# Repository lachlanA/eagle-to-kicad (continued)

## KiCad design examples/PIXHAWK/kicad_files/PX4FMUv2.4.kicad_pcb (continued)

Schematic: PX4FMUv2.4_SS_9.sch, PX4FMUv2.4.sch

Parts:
C901, C902, C903: 0u1; PIXHAWK2_0402-CAP
D1: MSS1P4-M3; PIXHAWK2_MICROSMP
D901, D902, D903: PESD0402-140; PIXHAWK2_0402-TVS
J901: PIXHAWK2_3X16RA
L901: KNH16C104DA5TS; PIXHAWK2_KYOCERA-KNH16-DA
R901: 10K; PIXHAWK2_0402-RES
R902, R903, R904, R905, R906, R907, R908, R909, R910, R911, R912, R913, R914, R915, R916, R917: 220R; PIXHAWK2_0402-RES
R918, R919, R922: 10K/0.1%; PIXHAWK2_0402-RES
U901, U902: TXS0108QFN20; PIXHAWK2_QFN20-RGY
U903: 74LVC2G240; PIXHAWK2_TSSOP8_SOT505-2

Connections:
!SBUS_OUTPUT_EN: U903.7 (!2OE); also elsewhere on the board
FMU-CH1: U901.7 (A6); also elsewhere on the board
FMU-CH1-PROT: J901.46, R913.P$2 (2)
FMU-CH2: U901.6 (A5); also elsewhere on the board
FMU-CH3: U901.5 (A4); also elsewhere on the board
FMU-CH4: U901.4 (A3); also elsewhere on the board
FMU-CH5: U901.3 (A2); also elsewhere on the board
FMU-CH6: U901.1 (A1); also elsewhere on the board
FMU-CH6-PROT: J901.31, R902.P$2 (2)
FMU-VDD_3V3: C902.P$1 (1), U901.2 (VCCA), U901.10 (OE), U901.19 (VCCB); also elsewhere on the board
GND: C901.P$2 (2), C902.P$2 (2), C903.P$2 (2), D901.A, D902.A, D903.A, J901.3, J901.6, J901.9, J901.12, J901.15, J901.18, J901.21, J901.24, J901.27, J901.30, J901.33, J901.36, J901.39, J901.42, J901.45, J901.48, L901.P$3, L901.P$4, L901.P$5, R919.P$1 (1), U901.11 (GND), U902.11 (GND), U903.1 (!1OE), U903.4 (GND); also elsewhere on the board
IO-CH1: U902.9 (A8); also elsewhere on the board
IO-CH1-PROT: J901.28, R917.P$2 (2)
IO-CH2: U902.8 (A7); also elsewhere on the board
IO-CH3: U902.7 (A6); also elsewhere on the board
IO-CH4: U902.6 (A5); also elsewhere on the board
IO-CH5: U902.5 (A4); also elsewhere on the board
IO-CH6: U902.4 (A3); also elsewhere on the board
IO-CH7: U902.3 (A2); also elsewhere on the board
IO-CH8: U902.1 (A1); also elsewhere on the board
IO-CH8-PROT: J901.7, R905.P$2 (2)
IO-VDD_3V3: C901.P$1 (1), C903.P$1 (1), U902.2 (VCCA), U902.10 (OE), U902.19 (VCCB), U903.8 (VCC); also elsewhere on the board
IO-VDD_5V5: J901.2; also elsewhere on the board
unnamed: R918.P$2 (2), R922.P$1 (1)
unnamed: J901.10, R914.P$2 (2)
unnamed: D902.C, R901.P$2 (2), R910.P$1 (1), U903.3 (2Y)
unnamed: R905.P$1 (1), U902.20 (B1)
unnamed: R914.P$1 (1), U902.18 (B2)
unnamed: R906.P$1 (1), U902.17 (B3)
unnamed: R915.P$1 (1), U902.16 (B4)
unnamed: R907.P$1 (1), U902.15 (B5)
unnamed: R916.P$1 (1), U902.14 (B6)
unnamed: R908.P$1 (1), U902.13 (B7)
unnamed: R917.P$1 (1), U902.12 (B8)
unnamed: R902.P$1 (1), U901.20 (B1)
unnamed: R911.P$1 (1), U901.18 (B2)
unnamed: R903.P$1 (1), U901.17 (B3)
unnamed: R912.P$1 (1), U901.16 (B4)
unnamed: R904.P$1 (1), U901.15 (B5)
unnamed: R913.P$1 (1), U901.14 (B6)
unnamed: J901.34, R911.P$2 (2)
unnamed: J901.13, R906.P$2 (2)
unnamed: J901.16, R915.P$2 (2)
unnamed: J901.19, R907.P$2 (2)
unnamed: J901.22, R916.P$2 (2)
unnamed: J901.25, R908.P$2 (2)
unnamed: J901.37, R903.P$2 (2)
unnamed: J901.40, R912.P$2 (2)
unnamed: J901.43, R904.P$2 (2)
unnamed: J901.4, R910.P$2 (2)
unnamed: D1.CATH (C), D903.C, L901.P$1
PPM-SBUS-PROT: J901.1, R909.P$2 (2)
PPM_INPUT: D901.C, R909.P$1 (1), U903.2 (1A); also elsewhere on the board
RSSI_IN: R901.P$1 (1); also elsewhere on the board
SBUS_INPUT: U903.6 (1Y); also elsewhere on the board
SBUS_OUTPUT: U903.5 (2A); also elsewhere on the board
VDD_SERVO: D1.ANOD (A), J901.5, J901.8, J901.11, J901.14, J901.17, J901.20, J901.23, J901.26, J901.29, J901.32, J901.35, J901.38, J901.41, J901.44, J901.47, R922.P$2 (2); also elsewhere on the board
VDD_SERVO_IN: L901.P$2; also elsewhere on the board
VDD_SERVO_SENS: R918.P$1 (1), R919.P$2 (2); also elsewhere on the board

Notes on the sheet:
Servo Header S.Bus interface
S.Bus in/out
Servo outputs

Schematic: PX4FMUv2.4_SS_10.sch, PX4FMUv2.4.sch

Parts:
C1001: 10u/25V; PIXHAWK2_0805-CAP
C1002: 10n; PIXHAWK2_0402-CAP
C1003: 1u0; PIXHAWK2_0603-CAP
C1004: 10u; PIXHAWK2_0603-CAP
C1005: 0u1F; PIXHAWK2_0402-CAP
C1008: 2u2; PIXHAWK2_0402-CAP
D1001: PMEG2005CT; PIXHAWK2_SOT23-3
F1001: 0ZCA0035FF2G; PIXHAWK2_PTC-1206
R1001: 100K; PIXHAWK2_0402-RES
R1002: 10K; PIXHAWK2_0402-RES
U1001: BQ24313; PIXHAWK2_QFN8-DSG
U1002: MIC5332; PIXHAWK2_MLF-8-EPAD

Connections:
GND: C1001.P$2 (2), C1002.P$2 (2), C1003.P$2 (2), C1004.P$2 (2), C1005.P$2 (2), C1008.P$2 (2), R1001.P$1 (1), R1002.P$1 (1), U1001.2 (VSS), U1001.5 (!CE), U1001.6 (VBAT), U1001.GND (VSS), U1001.P$2 (VSS), U1001.P$3 (VSS), U1002.2 (GND), U1002.GND; also elsewhere on the board
IO-!RESET: U1002.3 (POR2); also elsewhere on the board
IO-!VDD_SERVO_IN_FAULT: U1001.4 (!FAULT); also elsewhere on the board
IO-VDD_3V3: C1003.P$1 (1), C1004.P$1 (1), U1002.7 (VOUT2); also elsewhere on the board
IO-VDD_5V5: C1001.P$1 (1), C1005.P$1 (1), D1001.3 (CC), U1002.1 (VIN), U1002.4 (EN2); also elsewhere on the board
unnamed: D1001.2 (A2), U1001.8 (OUT)
unnamed: R1001.P$2 (2), U1001.7 (ILIM)
unnamed: D1001.1 (A1), F1001.2
unnamed: C1002.P$1 (1), U1002.6 (CSET)
VDD_3V3_SPEKTRUM: C1008.P$1 (1), U1002.8 (VOUT1); also elsewhere on the board
VDD_3V3_SPEKTRUM_EN: R1002.P$2 (2), U1002.5 (EN1); also elsewhere on the board
VDD_5V_IN: F1001.1; also elsewhere on the board
VDD_SERVO_IN: U1001.1 (IN); also elsewhere on the board

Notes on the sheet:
Dual supply from servo rail and FMU 5V rail
Current limit = 25 / Rilim (current in A, R in kOhms) 100K = 250mA
IO Power Supply
Reset output 1s / uF 10n = 10ms delay from power good to reset de-asserted.
Output voltage limited to 5.5V for input voltages up to 10.5V; output switches off at higher input voltages.

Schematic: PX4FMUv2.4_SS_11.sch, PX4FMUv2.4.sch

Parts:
C1101, C1102, C1103: 22u/25V; PIXHAWK2_0805-CAP
C1104: 100u; PIXHAWK2_1206-CAP
C1105, C1106, C1107: 0u1; PIXHAWK2_0402-CAP
C1108, C1109, C1110: 1000p/25V; PIXHAWK2_0402-CAP
J601: DF13C-6P-1.25V; CON-HIROSE-DF13_DF13C-6P-1.25V
L1101, L1102: KNH16C104DA5TS; PIXHAWK2_KYOCERA-KNH16-DA
R1101, R1102: 10K/0.1%; PIXHAWK2_0402-RES
R1103, R1104: 1M; PIXHAWK2_0402-RES
R1105, R1109, R1112: 453K; PIXHAWK2_0402-RES
R1106, R1110, R1113: 56K; PIXHAWK2_0402-RES
R1107, R1111, R1114: 105K; PIXHAWK2_0402-RES
R1115: 0R; PIXHAWK2_0402-RES
RN1101: 1M; RESISTOR-DIL_EXB28V
U1101: LTC4417; PIXHAWK2_MO-220
U1102, U1103, U1104: NTHD4102PT1G; PIXHAWK2_1206-8

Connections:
!VBUS_VALID: RN1101.2 (1), U1101.P$9 (!VALID3); also elsewhere on the board
!VDD_BRICK_VALID: RN1101.4 (1), U1101.P$7 (!VALID1); also elsewhere on the board
!VDD_SERVO_VALID: RN1101.3 (1), U1101.P$8 (!VALID2); also elsewhere on the board
BATT_CURRENT_SENS: R1101.P$1 (1); also elsewhere on the board
BATT_CURRENT_SENS_PROT: J601.3, L1101.P$1, R1104.P$1 (1)
BATT_VOLTAGE_SENS: R1102.P$1 (1); also elsewhere on the board
BATT_VOLTAGE_SENS_PROT: J601.4, L1102.P$1, R1103.P$1 (1)
GND: C1101.P$2 (2), C1102.P$2 (2), C1103.P$2 (2), C1104.P$2 (2), C1105.P$2 (2), C1106.P$2 (2), C1107.P$2 (2), C1108.P$2 (2), C1109.P$2 (2), C1110.P$2 (2), J601.5, J601.6, L1101.P$3, L1101.P$4, L1101.P$5, L1102.P$3, L1102.P$4, L1102.P$5, R1103.P$2 (2), R1104.P$2 (2), R1107.P$2 (2), R1111.P$2 (2), R1114.P$2 (2), R1115.P$1 (1), U1101.P$10 (GND), U1101.P$25 (GND); also elsewhere on the board
unnamed: C1108.P$1 (1), R1105.P$2 (2), R1106.P$1 (1), U1101.P$1 (UV1)
unnamed: R1106.P$2 (2), R1107.P$1 (1), U1101.P$2 (OV1)
unnamed: C1109.P$1 (1), R1109.P$2 (2), R1110.P$1 (1), U1101.P$3 (UV2)
unnamed: R1110.P$2 (2), R1111.P$1 (1), U1101.P$4 (OV2)
unnamed: R1113.P$2 (2), R1114.P$1 (1), U1101.P$6 (OV3)
unnamed: C1110.P$1 (1), R1112.P$2 (2), R1113.P$1 (1), U1101.P$5 (UV3)
unnamed: C1105.P$1 (1), U1101.P$18 (VS1), U1102.P$1 (S), U1102.P$3 (S)
unnamed: L1102.P$2, R1102.P$2 (2)
unnamed: L1101.P$2, R1101.P$2 (2)
unnamed: R1115.P$2 (2), U1101.P$24 (HYS)
unnamed: C1106.P$1 (1), U1101.P$16 (VS2), U1103.P$1 (S), U1103.P$3 (S)
unnamed: C1107.P$1 (1), U1101.P$14 (VS3), U1104.P$1 (S), U1104.P$3 (S)
unnamed: U1101.P$13 (G3), U1104.P$2 (G), U1104.P$4 (G)
unnamed: U1101.P$15 (G2), U1103.P$2 (G), U1103.P$4 (G)
unnamed: U1101.P$17 (G1), U1102.P$2 (G), U1102.P$4 (G)
VBUS: C1103.P$1 (1), R1112.P$1 (1), U1101.P$19 (V3), U1104.P$7 (D), U1104.P$8 (D); also elsewhere on the board
VDD_5V_BRICK: C1101.P$1 (1), J601.1, J601.2, R1105.P$1 (1), U1101.P$21 (V1), U1102.P$7 (D), U1102.P$8 (D); also elsewhere on the board
VDD_5V_IN: C1104.P$1 (1), RN1101.5 (2), RN1101.6 (2), RN1101.7 (2), U1101.P$12 (VOUT), U1102.P$5 (D), U1102.P$6 (D), U1103.P$5 (D), U1103.P$6 (D), U1104.P$5 (D), U1104.P$6 (D); also elsewhere on the board
VDD_SERVO: C1102.P$1 (1), R1109.P$1 (1), U1101.P$20 (V2), U1103.P$7 (D), U1103.P$8 (D); also elsewhere on the board

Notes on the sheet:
Power source selector
Resistors picked so that undervoltage lockout starts at 4.0V and overvoltage lockout at 5.75V. Use 1% or better accuracy!
POWER PATH CONTROLLER: Does enable output if valid for continous 256 ms

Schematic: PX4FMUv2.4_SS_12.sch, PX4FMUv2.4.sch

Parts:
!VBUS_VALID1116: PAD.04; PIXHAWK2_PAD.04X.04
!VDD_BRICK_VALID1116: PAD.04; PIXHAWK2_PAD.04X.04
!VDD_SERVO_VALID1116: PAD.04; PIXHAWK2_PAD.04X.04
ADC_PR1116: PAD.04; PIXHAWK2_PAD.04X.04
CAN_H1116: PAD.04; PIXHAWK2_PAD.04X.04
CAN_L1116: PAD.04; PIXHAWK2_PAD.04X.04
FMU-BOOT1101: PAD.04; PIXHAWK2_PAD.04X.04
GND1116, GND.1116: PAD.04; PIXHAWK2_PAD.04X.04
IO-BOOT1101: PAD.04; PIXHAWK2_PAD.04X.04
JP1, JP2: FIDUCIAL1.5X3; PIXHAWK2_FIDUCIAL-1.5X3
M3_MOUNT1101, M3_MOUNT1102, M3_MOUNT1103, M3_MOUNT1104: MOUNT-HOLE3.1MM; PIXHAWK2_MOUNT-HOLE3.1
OSHW_LOGO1116: OSHW-LOGOS; PIXHAWK2_OSHW-LOGO-S
S1RX1116, S1TX1116, S2RX1116, S2TX1116, S3RX1116, S3TX1116, S4RX1116, S4TX1116, S5_RX1116, S5_TX1116: PAD.04; PIXHAWK2_PAD.04X.04
VBUS1116: PAD.04; PIXHAWK2_PAD.04X.04
VDDA_3V1101: PAD.04; PIXHAWK2_PAD.04X.04
VDD_3V1101, VDD_5V_BRICK1116, VDD_5V_IN1116: PAD.04; PIXHAWK2_PAD.04X.04
VDD_SERVO1116: PAD.04; PIXHAWK2_PAD.04X.04
VP_0, VP_1, VP_2, VP_3, VP_33, VP_34, VP_35, VP_41, VP_42, VP_43, VP_51, VP_52, VP_53, VP_54, VP_55, VP_56, VP_57, VP_58, VP_59, VP_60, VP_61: VPDEV0; VPAD_VPAC0
VP_4, VP_5, VP_6, VP_7, VP_8, VP_9, VP_10, VP_11, VP_12, VP_13, VP_14, VP_15, VP_16, VP_17, VP_18, VP_19, VP_20, VP_21, VP_22, VP_23, VP_24, VP_25, VP_26, VP_27, VP_28, VP_29, VP_30, VP_31, VP_32, VP_36, VP_37, VP_39, VP_40, VP_44, VP_45, VP_46, VP_47, VP_48, VP_49, VP_50: VPDEV1; VPAD_VPAC1
VP_38: VPDEV2; VPAD_VPAC2

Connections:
!VBUS_VALID: !VBUS_VALID1116.P$1; also elsewhere on the board
!VDD_BRICK_VALID: !VDD_BRICK_VALID1116.P$1; also elsewhere on the board
!VDD_SERVO_VALID: !VDD_SERVO_VALID1116.P$1; also elsewhere on the board
CAN_H: CAN_H1116.P$1; also elsewhere on the board
CAN_L: CAN_L1116.P$1; also elsewhere on the board
FMU-BOOT0: FMU-BOOT1101.P$1; also elsewhere on the board
FMU-VDD_3V3: VDD_3V1101.P$1; also elsewhere on the board
GND: GND1116.P$1, GND.1116.P$1, VP_0.VP, VP_1.VP, VP_2.VP, VP_3.VP, VP_4.VP, VP_5.VP, VP_6.VP, VP_7.VP, VP_8.VP, VP_9.VP, VP_10.VP, VP_11.VP, VP_12.VP, VP_13.VP, VP_14.VP, VP_15.VP, VP_16.VP, VP_17.VP, VP_18.VP, VP_19.VP, VP_20.VP, VP_21.VP, VP_22.VP, VP_23.VP, VP_24.VP, VP_25.VP, VP_26.VP, VP_27.VP, VP_28.VP, VP_29.VP, VP_30.VP; also elsewhere on the board
IO-BOOT0: IO-BOOT1101.P$1; also elsewhere on the board
IO-VDD_3V3: VP_31.VP, VP_32.VP; also elsewhere on the board
PRESSURE_SENS_IN: ADC_PR1116.P$1; also elsewhere on the board
SERIAL1_RX: S1RX1116.P$1; also elsewhere on the board
SERIAL1_TX: S1TX1116.P$1; also elsewhere on the board
SERIAL2_RX: S2RX1116.P$1; also elsewhere on the board
SERIAL2_TX: S2TX1116.P$1; also elsewhere on the board
SERIAL3_RX: S3RX1116.P$1; also elsewhere on the board
SERIAL3_TX: S3TX1116.P$1; also elsewhere on the board
SERIAL4_RX: S4RX1116.P$1; also elsewhere on the board
SERIAL4_TX: S4TX1116.P$1; also elsewhere on the board
SERIAL5_RX: S5_RX1116.P$1; also elsewhere on the board
SERIAL5_TX: S5_TX1116.P$1; also elsewhere on the board
VBUS: VBUS1116.P$1, VP_33.VP, VP_34.VP, VP_35.VP; also elsewhere on the board
VDD_3V3_SENSORS: VDDA_3V1101.P$1, VP_36.VP, VP_37.VP; also elsewhere on the board
VDD_5V_BRICK: VDD_5V_BRICK1116.P$1, VP_38.VP, VP_39.VP, VP_40.VP; also elsewhere on the board
VDD_5V_IN: VDD_5V_IN1116.P$1, VP_41.VP, VP_42.VP, VP_43.VP, VP_44.VP, VP_45.VP, VP_46.VP, VP_47.VP, VP_48.VP, VP_49.VP, VP_50.VP, VP_51.VP, VP_52.VP, VP_53.VP; also elsewhere on the board
VDD_5V_PERIPH: VP_54.VP, VP_55.VP, VP_56.VP, VP_57.VP, VP_58.VP; also elsewhere on the board
VDD_SERVO: VDD_SERVO1116.P$1, VP_59.VP, VP_60.VP, VP_61.VP; also elsewhere on the board

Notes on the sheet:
Mounting holes to suit M3 fastener
and Richco R908 series spacer.
Use R908-5 spacers to stack with
other PX4 series boards (7.95 mm).
Production Testing Pads
Test and Fiducials
Minimum drill: 0.3 mm
Minimum trace width (use mm for traces): 0.15 mm
Minimum copper distance (all signals): 0.15 mm
Dimension / hole minimum distance: 0.2 mm
Layout grid: 4 mil, part grid: 4 mil. Dimensions / hole positions: 0.5 mm
Board: FR4 black, 1.0 mm. Solder stop on vias < 0.6 mm.
Signoff rules: Footprint checked, pinmap checked, schematic checked, cross-references to other pages checked.
Routing: 1: general/escape 2: ground 3: horizontal 4: vertical 5: power 6: general/escape
Fiducials for machine vision alignment.
Parts: Resistors: 0402 / 1% unless specified otherwise Capacitors: 0402 to 1206, ceramic, voltage rating: 10V unless specified

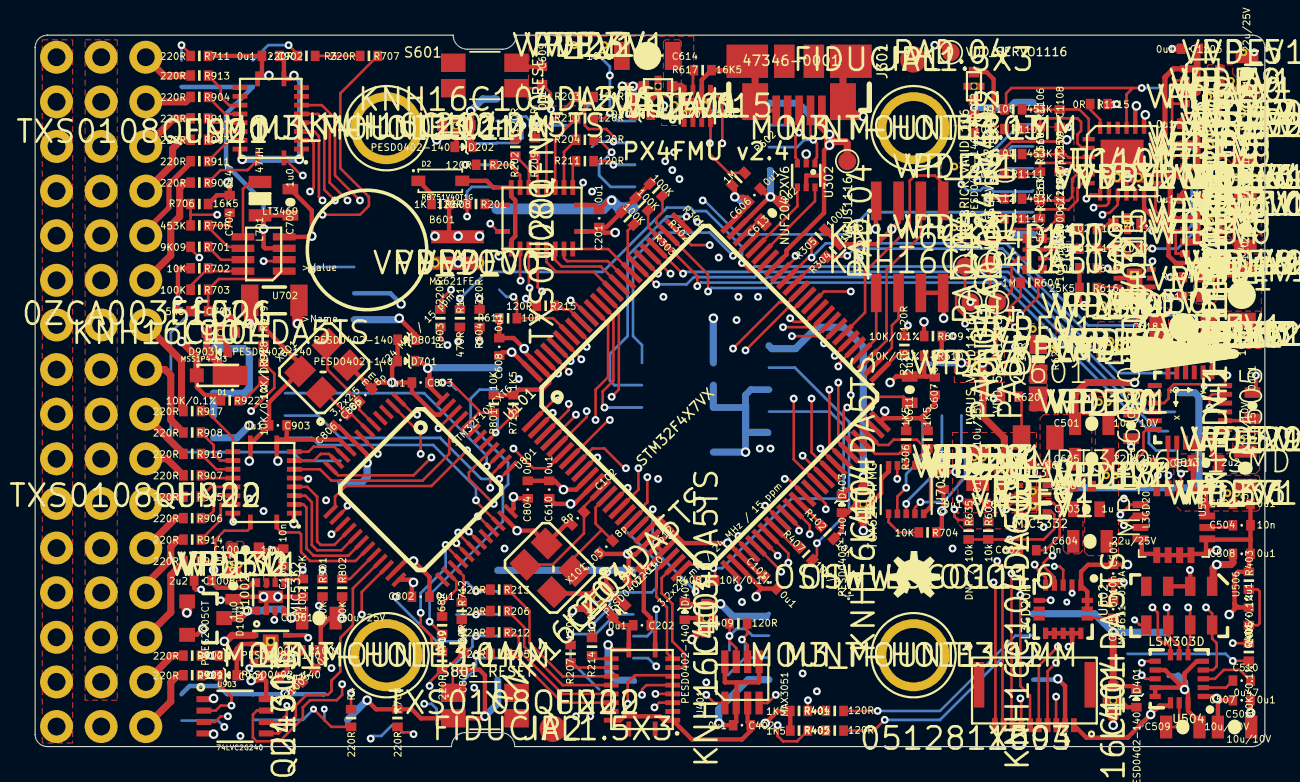
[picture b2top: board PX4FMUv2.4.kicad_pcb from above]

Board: 6 copper layers, 70.0 x 40.5 mm, 354 parts (0 on the bottom side), 262 nets.

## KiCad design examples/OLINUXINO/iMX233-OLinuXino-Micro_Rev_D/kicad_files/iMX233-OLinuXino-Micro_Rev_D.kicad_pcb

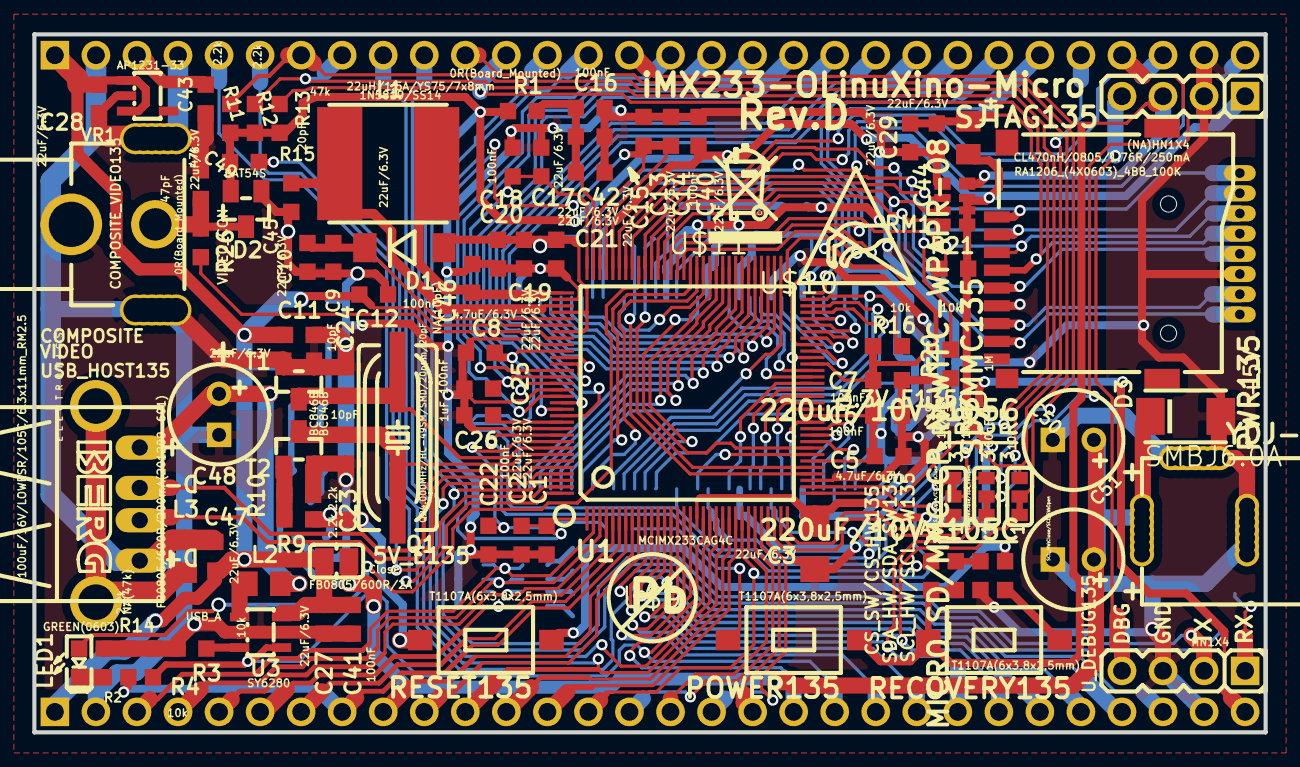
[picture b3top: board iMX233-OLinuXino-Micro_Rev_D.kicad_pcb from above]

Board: 4 copper layers, 76.2 x 43.2 mm, 124 parts (0 on the bottom side), 143 nets.

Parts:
3.3V_E135: Open; SJ_1_SMALLER
5V_E135: Close; SJ-CLOSE
C1, C2, C9, C10, C11, C13, C15, C17, C19, C20, C21, C27, C28, C29, C40, C42, C43, C44, C47: 22uF/6.3V; C0603_DWS
C3: 22uF/6.3V; C1206
C4, C6, C7, C12, C14, C16, C18, C22, C25, C30, C31, C32, C33, C34, C35, C36, C37, C38, C39, C41: 100nF; C0603_DWS
C5, C8: 4.7uF/6.3V; C0603_DWS
C23, C24: 10pF; C0603_DWS
C26: 1uF; C0603_DWS
C45: 20pF; C0603_DWS
C46: NA(10pF); C0603_DWS
C48: 100uF/16V/LOWESR/105C/6.3x11mm_RM2.5; E2,5-6,3
C49: 47pF; C0603_DWS
C50, C51: 220uF/10V/105C; E2,5-6,3
COMPOSITE_VIDEO135: VIDEO_CON; VIDEO_CINCH
CON1, CON2: NA(HN1X30); HN1X30
CS_SW/CS_HW135: CS_SW:Open/CS_HW:Close; SJ_2_SMALL
D00_H135, D03_H135: Close; SJ_1_SMALLER
D1: 1N5819/SS14; MLL-41
D01_H135, D02_H135: Open; SJ_1_SMALLER
D2: BAT54S; SOT23C(BAT54S)
D3: SMBJ6.0A; DO214AA
D4: BAT54C; SOT23C
FET1: NA(IRLML6402); SOT23
JTAG135: NA(WU08S); WU08S
L1: 22uH/1.5A/YS75/7x8mm; L7078
L2: FB0805/600R/2A; L0805_5MIL_DWS
L3: FB0805/600R/200mA(201209-601); L0805_5MIL_DWS
L4: CL470nH/0805/1.76R/250mA; L0805_5MIL_DWS
LED1: GREEN(0603); LED-0603
POWER135: T1107A(6x3,8x2,5mm); SW-TAKT_6X3.5_SMD
PWR135: YDJ-1136; PWR_JACK_UNI_MILLING
Q1: Q24.000MHz/HC-49SM/SMD/20ppm/20pF; HC49%2fSMD2_THIN
R1, R6, R26: 0R(Board_Mounted); 0603_0R
R2, R9, R10, R11, R12: 2.2k; R0603_5MIL_DWS
R3, R4, R5, R16, R21: 10k; R0603_5MIL_DWS
R7, R8, R18, R19: 1k/1%; R0603_5MIL_DWS
R13, R15: 47k; R0603_5MIL_DWS
R14, R25: NA(47k); R0603_5MIL_DWS
R17: NA(120R); R0603_5MIL_DWS
R20: 1M; R0603_5MIL_DWS
R22: 4.7k; R0603_5MIL_DWS
RECOVERY135: T1107A(6x3,8x2,5mm); SW-TAKT_6X3.5_SMD
RESET135: T1107A(6x3,8x2,5mm); SW-TAKT_6X3.5_SMD
RM1: RA1206_(4X0603)_4B8_100K; R_MATRIX_4
RM2: RA1206_(4X0603)_4B8_47K; R_MATRIX_4
RM3: RA1206_(4X0603)_4B8_4.7K; R_MATRIX_4
SCL_HW/SCL_SW135: SCL_HW:Close/SCL_SW:Open; SJ_2_SMALL
SD/MMC135: MICRO_SD/MMC_CP_NEWTFC-WPAPR-08; TFC-WPAPR-08
SDA_HW/SDA_SW135: SDA_HW:Close/SDA_SW:Open; SJ_2_SMALL
SJTAG135: (NA)HN1X4; HN1X4
T1, T2: BC846B; SOT23
T3: NA(DTA114YKA); SOT-23
T4: NA(DTC114YKA); SOT-23
U1: MCIMX233CAG4C; TQFP128LD
U2: HY5DU121622D(L)T(P)-J; 66TSOP-II
U3: SY6280; SOT23-5
U$5: LOGO-OPENHARDWARE_8X8
U$8: OLIMEX1_V
U$9: PB
U$10: ESD_SYMBOL
U$11: RECYCLE_BIN1%2f8
U$12: ROHS
USB_HOST135: USB_A; USB_PN87520_HOST_PTH
U_DEBUG135: HN1X4
VR1: AP1231-33; SOT-23-5

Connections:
+5V: 5V_E135.2, C11.2, C12.2, C27.1, C28.1, C41.1, C47.1, CON1.1, CON2.1, FET1.3, U1.102, U3.5, VR1.1, VR1.3
+24V: C19.2, C20.2, C21.2, CON2.30, D1.A, U1.100, U1.103
/+5V_HOST_PWR: C48.+, L2.1, USB_HOST135.1
/A0: U1.76, U2.29
/A1: U1.75, U2.30
/A2: U1.74, U2.31
/A3: U1.73, U2.32
/A4: U1.72, U2.35
/A5: U1.71, U2.36
/A6: U1.70, U2.37
/A7: U1.69, U2.38
/A8: U1.68, U2.39
/A9: U1.67, U2.40
/A10: U1.66, U2.28
/A11: U1.65, U2.41
/A12: U1.64, U2.42
/AUART1_RXD: CON2.6, U1.128
/AUART1_TXD: CON2.5, U1.127
/BA0: U1.79, U2.26
/BA1: U1.80, U2.27
/CASN: U1.61, U2.22
/CKE: U1.78, U2.44
/CLK: R17.2, U1.36, U2.45
/CLKN: R17.1, U1.37, U2.46
/CS: R16.1, U1.63, U2.24
/CS_UEXT: CS_SW/CS_HW135.1, U1.32
/CS_UEXT_GPIO: CON2.12, CS_SW/CS_HW135.2, R13.1
/D0: U1.41, U2.2
/D1: U1.43, U2.4
/D2: U1.42, U2.5
/D3: U1.44, U2.7
/D4: U1.47, U2.8
/D5: U1.48, U2.10
/D6: U1.49, U2.11
/D7: U1.50, U2.13
/D8: U1.51, U2.54
/D9: U1.52, U2.56
/D10: U1.54, U2.57
/D11: U1.55, U2.59
/D12: U1.57, U2.60
/D13: U1.58, U2.62
/D14: U1.60, U2.63
/D15: U1.59, U2.65
/DCDC_VDDA: C17.2, C18.2, C25.2, U1.96, U1.110
/DCDC_VDDD: C1.2, C2.2, C13.2, C14.2, U1.1, U1.93, U1.94
/DCDC_VDDIO: C15.2, C16.2, C42.2, R1.2, U1.95
/DEBUG: SJTAG135.4, U1.89, U_DEBUG135.4
/DQM0: U1.46, U2.20
/DQM1: U1.56, U2.47
/DQS0: U1.39, U2.16
/DQS1: U1.40, U2.51
/HPL: CON2.16, U1.113
/HPR: CON2.17, U1.109
/HP_VGND: CON2.18, U1.111
/I2C_SCL: CON2.7, R11.1, SCL_HW/SCL_SW135.2
/I2C_SDA: CON2.8, R12.1, SDA_HW/SDA_SW135.2
/LED1: LED1.A, U1.88
/LIN1_INL: CON2.19, U1.115
/LIN1_INR: CON2.20, U1.114
/N$1: POWER135.P$1, R6.1
/N$2: 3.3V_E135.1, CON1.30
/N$3: 5V_E135.1, C50.+, C51.+, D3.C, FET1.2, PWR135.+, T3.2
/N$4: C49.1, COMPOSITE_VIDEO135.IO, D2.3, R26.2
/N$5: L2.2, U3.1
/N$6: R3.2, U3.3
/N$7: C38.2, C39.2, R18.1, R19.2, U2.49
/N$9: R5.1, RECOVERY135.P$1
/N$11: D4.3, U_DEBUG135.1
/N$12: FET1.1, R25.2, T3.3
/N$14: T3.1, T4.3
/N$18: C46.2, L1.2, U1.97
/N$19: C45.2, L1.1, U1.99
/N$25: C26.2, U1.117
/N$38: C4.1, R8.1
/N$42: LED1.C, R2.2
/N$43: R9.1, R10.1, T2.1
/N$101: D03_H135.1, RM3.4.1
/N$103: D02_H135.1, RM3.3.1
/N$104: D01_H135.1, RM3.2.1
/N$105: D00_H135.1, RM3.1.1
/N$266: L3.2, USB_HOST135.P$1, USB_HOST135.P$2
/PIN1/LCD_D00: CON1.3, RM2.1.1, RM3.1.2, U1.2
/PIN2/LCD_D01: CON1.4, RM2.2.1, RM3.2.2, U1.3
/PIN3/LCD_D02: CON1.5, RM2.3.1, RM3.3.2, U1.4
/PIN4/LCD_D03: CON1.6, RM2.4.1, RM3.4.2, U1.5
/PIN5/LCD_D04: CON1.7, U1.6
/PIN6/LCD_D05: CON1.8, R14.2, U1.7
/PIN7/LCD_D06: CON1.9, U1.8
/PIN8/LCD_D07: CON1.10, U1.9
/PIN9/LCD_D08/SSP2_MISO: CON1.11, CON2.9, U1.22
/PIN10/LCD_D09: CON1.12, U1.23
/PIN11/LCD_D10: CON1.13, U1.24
/PIN12/LCD_D11: CON1.14, CS_SW/CS_HW135.3, U1.25
/PIN13/LCD_D12: CON1.15, U1.27
/PIN14/LCD_D13: CON1.16, U1.26
/PIN15/LCD_D14: CON1.17, U1.29
/PIN16/LCD_D15: CON1.18, U1.28
/PIN17/LCD_D16: CON1.19, U1.19
/PIN18/LCD_D17/USB_EN: CON1.20, R4.2, U1.20, U3.4
/PIN19/LCD_DOTCLK: CON1.21, U1.17
/PIN20/LCD_VSYNC: CON1.22, U1.16
/PIN21/LCD_HSYNC/I2C_SDA: CON1.23, SDA_HW/SDA_SW135.1, U1.15
/PIN22/LCD_EN/I2C_SCL: CON1.24, SCL_HW/SCL_SW135.1, U1.11
/PIN23/LCD_DISP: CON1.25, U1.12
/PIN24/LCD_WR: CON1.26, U1.13
/PIN25/LCD_RS: CON1.27, R15.2, U1.14
/PIN26/LCD_CS: CON1.28, U1.10
/PIN27/PWM2: CON2.28, U1.91
/PIN28/SOFT_SDA: CON2.27, SDA_HW/SDA_SW135.3, U1.31
/PIN29/SOFT_SCL: CON2.26, SCL_HW/SCL_SW135.3, U1.34
/PIN30: CON2.25, U1.81
/PIN31: CON2.24, U1.82
/PIN32/LRADC1: CON2.23, U1.107
/PIN33/LRADC0: CON2.22, U1.108
/PIN34/MIC: CON2.21, U1.116
/PSWITCH: R7.1, U1.119
/PWM0/DUART_RXD: CON2.13, D4.2, R22.2, U1.125
/PWM1/DUART_TXD: CON2.14, U1.126, U_DEBUG135.2
/RASN: U1.62, U2.23
/RESET: R9.2, RESET135.P$1, T4.1
/SD_VCC: C29.2, C44.2, JTAG135.5, L4.2, SD/MMC135.4
/SJTAG_PSW: CON2.15, POWER135.P$2, R7.2, R8.2, RECOVERY135.P$2, RM1.1.2, SJTAG135.3
/SSP1_CMD: JTAG135.6, R21.1, SD/MMC135.3, U1.83
/SSP1_DATA0: JTAG135.2, RM1.4.1, SD/MMC135.7, U1.84
/SSP1_DATA1: JTAG135.1, RM1.3.1, SD/MMC135.8, U1.85
/SSP1_DATA2: JTAG135.8, RM1.2.1, SD/MMC135.1, U1.86
/SSP1_DATA3: JTAG135.7, R20.1, SD/MMC135.2, U1.87
/SSP1_SCK: JTAG135.4, SD/MMC135.5, U1.90
/SSP2_MOSI: CON2.10, U1.21
/SSP2_SCK: CON2.11, U1.33
/USB_DM: U1.123, USB_HOST135.2
/USB_DP: U1.124, USB_HOST135.3
/VDAC1: R26.1, U1.104
/VDD4P2: C9.2, C10.2, D1.K, U1.101
/VDDXTAL: C22.2, R6.2, U1.120
/WEN: U1.77, U2.21
/XTALI: C23.2, Q1.2, T2.3, U1.122
/XTALO: C24.2, Q1.1, T1.3, U1.121
GND: C1.1, C2.1, C3.1, C4.2, C5.1, C6.1, C7.1, C8.1, C9.1, C10.1, C11.1, C12.1, C13.1, C14.1, C15.1, C16.1, C17.1, C18.1, C19.1, C20.1, C21.1, C22.1, C23.1, C24.1, C25.1, C26.1, C27.2, C28.2, C29.1, C30.1, C31.1, C32.1, C33.1, C34.1, C35.1, C36.1, C37.1, C39.1, C40.1, C41.2, C42.1, C43.2, C44.1, C45.1, C46.1, C47.2, C48.-, C49.2, C50.-, C51.-, COMPOSITE_VIDEO135.GND1, COMPOSITE_VIDEO135.GND2, COMPOSITE_VIDEO135.GND3, COMPOSITE_VIDEO135.GNG3, CON1.2, CON1.29, CON2.2, CON2.4, CON2.29, D2.1, D3.A, JTAG135.3, L3.1, PWR135.-, PWR135.--, R2.1, R3.1, R4.1, R10.2, R14.1, R19.1, R20.2, R25.1, RM1.1.1, RM2.1.2, RM2.2.2, RM2.3.2, RM2.4.2, SD/MMC135.6, SJTAG135.2, T1.1, T1.2, T2.2, T4.2, U1.30, U1.35, U1.98, U1.105, U1.112, U1.118, U2.6, U2.12, U2.34, U2.48, U2.52, U2.58, U2.64, U2.66, U3.2, USB_HOST135.4, U_DEBUG135.3, VR1.2
unnamed: SD/MMC135.10, SD/MMC135.11, SD/MMC135.12, SD/MMC135.13
V+: C5.2, C6.2, C7.2, C8.2, C30.2, C31.2, C32.2, C33.2, C34.2, C35.2, C36.2, C37.2, C38.1, R16.2, R18.2, U1.38, U1.45, U1.53, U1.106, U2.1, U2.3, U2.9, U2.15, U2.18, U2.33, U2.55, U2.61
VCC: 3.3V_E135.2, C3.2, C40.2, D00_H135.2, D01_H135.2, D2.2, D02_H135.2, D03_H135.2, L4.1, R1.1, R5.2, R11.2, R12.2, R13.2, R15.1, R21.2, R22.1, RESET135.P$2, RM1.2.2, RM1.3.2, RM1.4.2, SJTAG135.1, U1.18, U1.92
VPP: C43.1, CON2.3, VR1.5

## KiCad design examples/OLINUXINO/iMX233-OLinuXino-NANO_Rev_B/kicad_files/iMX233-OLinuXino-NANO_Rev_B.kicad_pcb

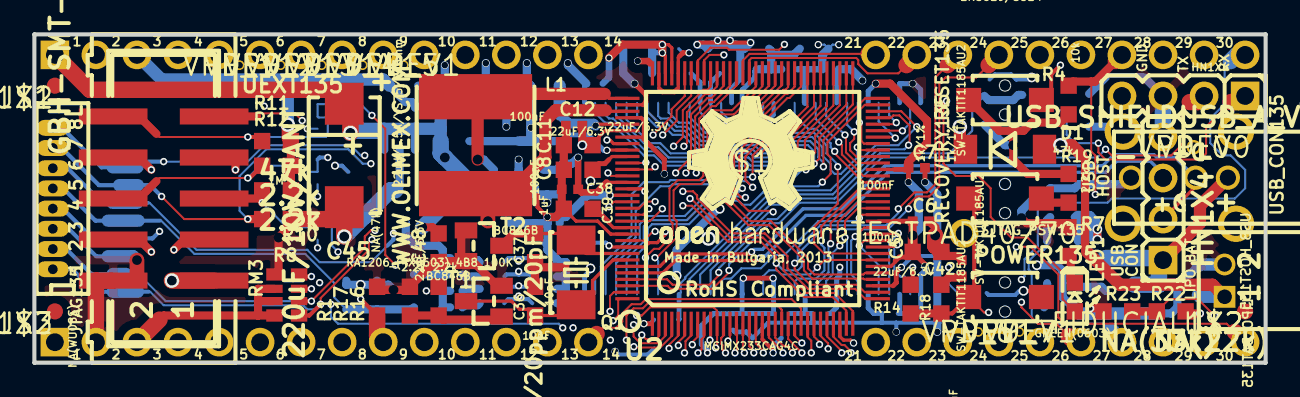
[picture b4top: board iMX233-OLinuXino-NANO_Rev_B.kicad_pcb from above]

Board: 6 copper layers, 76.2 x 20.3 mm, 132 parts (0 on the bottom side), 136 nets.

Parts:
0, 3: Close; SJ_1_SMALLER
1, 2: Open; SJ_1_SMALLER
C1, C2, C3, C4, C5, C8, C9, C10, C11, C13, C15, C17, C26, C29, C31, C32, C40, C41, C43, C48, C49, C50, C51, C52, C53: 22uF/6.3V; C0603_DWS
C6, C7, C12, C14, C16, C18, C19, C20, C21, C22, C23, C24, C25, C27, C28, C30, C35, C38, C42: 100nF; C0402_TI
C33: NA(10pF); C0603_DWS
C34: 100pF; C0603_DWS
C36, C37: 10pF; C0603_DWS
C39: 1uF; C0603_DWS
C44: 47pF; C0603_DWS
C45: 220uF/10V/TANT; CT7343
C47: 100nF; C0603_DWS
CH/CS135: SCL_HW:Open/SCL_SW:Close; SJ_2_SMALLER
CON1, CON2: HN1X30_WITHOUT(15-20)
CSS/CSH135: CS_SW:Open/CS_HW:Close; SJ_2_SMALLER
D1: 1N5819/SS14; MLL-41
D2: BAT54C; SOT23C
D3: SMBJ6.0A; DO214AA
DH/DS135: SDA_HW:Open/SDA_SW:Close; SJ_2_SMALLER
JTAG135: NA(WU08S); WU08S
L1: 22uH/1.5A/YS75/7x8mm; L7078
L2: CL470nH/0805/1.76R/250mA; L0805_5MIL_DWS
L3: FB0805/600R/2A; L0805_5MIL_DWS
L4: FB0805/600R/200mA(201209-601); L0805_5MIL_DWS
LED1: GREEN(0603); LED-0603
LIPO_BAT135: CON2DW02R; DW02R
POWER135: SW-TAKTIT1185AU2; IT1185AU2
Q1: 4SB24.000F20E15/5x3.2mm/20ppm/20pF; HCX-4S
R1: NA(47k); R0603_5MIL_DWS
R2, R9, R19, R20, R21: 10k; R0603_5MIL_DWS
R3: NA(120R); R0603_5MIL_DWS
R4, R11: 47k; R0603_5MIL_DWS
R5, R6, R14, R18: 1k/1%; R0603_5MIL_DWS
R7, R10, R12, R16, R17: 2.2k; R0603_5MIL_DWS
R8: 1M; R0603_5MIL_DWS
R13: 4.7k; R0603_5MIL_DWS
R15: 0R(Board_Mounted); 0603_0R
R22: NA(22k); R0603_5MIL_DWS
R23: NA(33k); R0603_5MIL_DWS
RECOVERY135: SW-TAKTIT1185AU2; IT1185AU2
RESET135: SW-TAKTIT1185AU2; IT1185AU2
RM1: RA1206_(4X0603)_4B8_4.7K; R_MATRIX_4
RM2: RA1206_(4X0603)_4B8_47K; R_MATRIX_4
RM3: RA1206_(4X0603)_4B8_100K; R_MATRIX_4
SD135: MICRO_SD/MMC_NEW; TFR%2fC-MEM-CON
SJTAG_PSW135: TESTPAD40/70; TESTPAD
T1, T2: BC846B; SOT23
U1: HY5DU121622D(L)T(P)-J; 66TSOP-II
U2: MCIMX233CAG4C; TQFP128LD
U3: SY6280; SOT23-5
U$1, U$2, U$3, U$7, U$13, U$14: FIDUCIAL1X2; FIDUCIAL-1X2
U$4: ESD_SYMBOL
U$6: RECYCLE_BIN1%2f8
U$8: OLIMEX1_V
U$15: PB
U$18: LOGO-OPENHARDWARE_8X8
UEXT135: GBH-SMT-10; ML10_S
USB_CON135: HN1X4
USB_HOST135: USB_SHIELDUSB_A_VERTICAL; USB_A_VERTICAL_PTH
U_DEBUG135: HN1X4
VP_0: VPDEV0; VPAC0
VP_1, VP_2, VP_3, VP_4, VP_5, VP_6, VP_7: VPDEV1; VPAC1
VR1: AP1231-33; SOT-23-5

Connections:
+5V: C11.2, C12.2, C45.+, C47.1, C48.1, C49.1, C50.1, CON2.1, D3.C, R22.2, U2.102, U3.5, VR1.1, VR1.3
+24V: C29.2, C31.2, C32.2, C43.1, CON1.1, D1.A, LIPO_BAT135.1, U2.100, U2.103
/+5V_HOST_PWR: C52.1, C53.1, L3.1, USB_CON135.1, USB_HOST135.1
/A0: U1.29, U2.76
/A1: U1.30, U2.75
/A2: U1.31, U2.74
/A3: U1.32, U2.73
/A4: U1.35, U2.72
/A5: U1.36, U2.71
/A6: U1.37, U2.70
/A7: U1.38, U2.69
/A8: U1.39, U2.68
/A9: U1.40, U2.67
/A10: U1.28, U2.66
/A11: U1.41, U2.65
/A12: U1.42, U2.64
/AUART1_RXD: U2.128, UEXT135.4
/AUART1_TXD: U2.127, UEXT135.3
/BA0: U1.26, U2.79
/BA1: U1.27, U2.80
/CASN: U1.22, U2.61
/CKE: U1.44, U2.78
/CLK: R3.2, U1.45, U2.36
/CLKN: R3.1, U1.46, U2.37
/CS: R2.1, U1.24, U2.63
/CS_UEXT: CSS/CSH135.1, U2.32
/CS_UEXT_GPIO: CSS/CSH135.2, R11.1, UEXT135.10
/D0: U1.2, U2.41
/D1: U1.4, U2.43
/D2: U1.5, U2.42
/D3: U1.7, U2.44
/D4: U1.8, U2.47
/D5: U1.10, U2.48
/D6: U1.11, U2.49
/D7: U1.13, U2.50
/D8: U1.54, U2.51
/D9: U1.56, U2.52
/D10: U1.57, U2.54
/D11: U1.59, U2.55
/D12: U1.60, U2.57
/D13: U1.62, U2.58
/D14: U1.63, U2.60
/D15: U1.65, U2.59
/DCDC_VDDA: C26.2, C27.2, C38.2, U2.96, U2.110
/DCDC_VDDD: C1.2, C2.2, C13.2, C14.2, U2.1, U2.93, U2.94
/DEBUG: U2.89, U_DEBUG135.4
/DQM0: U1.20, U2.46
/DQM1: U1.47, U2.56
/DQS0: U1.16, U2.39
/DQS1: U1.51, U2.40
/HPL: CON2.7, U2.113
/HPR: CON2.8, U2.109
/HP_VGND: CON2.9, U2.111
/I2C_SCL: CH/CS135.2, R10.1, UEXT135.5
/I2C_SDA: DH/DS135.2, R12.1, UEXT135.6
/LED1: LED1.A, U2.88
/LIN1_INL: CON2.10, U2.115
/LIN1_INR: CON2.11, U2.114
/N$1: POWER135.1, R15.1
/N$3: L3.2, U3.1
/N$6: R20.2, U3.3
/N$7: C28.2, C30.2, R5.1, R6.2, U1.49
/N$9: R19.1, RECOVERY135.1
/N$11: D2.3, U_DEBUG135.1
/N$18: C33.2, L1.2, U2.97
/N$19: C34.2, L1.1, U2.99
/N$25: C39.2, U2.117
/N$38: C42.1, R18.1
/N$42: LED1.C, R7.2
/N$43: R16.1, R17.1, T1.1
/N$101: 3.1, RM1.4.1
/N$103: 2.1, RM1.3.1
/N$104: 1.1, RM1.2.1
/N$105: 0.1, RM1.1.1
/N$266: L4.2, USB_HOST135.P$3, USB_HOST135.P$4
/PIN1/LCD_D00: CON1.4, RM1.1.2, RM2.1.1, U2.2
/PIN2/LCD_D01: CON1.5, RM1.2.2, RM2.2.1, U2.3
/PIN3/LCD_D02: CON1.6, RM1.3.2, RM2.3.1, U2.4
/PIN4/LCD_D03: CON1.7, RM1.4.2, RM2.4.1, U2.5
/PIN5/LCD_D04: CON1.8, U2.6
/PIN6/LCD_D05: CON1.9, R1.2, U2.7
/PIN7/LCD_D06: CON1.10, U2.8
/PIN8/LCD_D07: CON1.11, U2.9
/PIN9/LCD_D08/SSP2_MISO: CON1.12, U2.22, UEXT135.7
/PIN10/LCD_D09: CON1.13, U2.23
/PIN11/LCD_D10: CON1.14, U2.24
/PIN12/LCD_D11: CON1.21, CSS/CSH135.3, U2.25
/PIN13/LCD_D12: CON1.22, U2.27
/PIN14/LCD_D13: CON1.23, U2.26
/PIN15/LCD_D14: CON1.24, U2.29
/PIN16/LCD_D15: CON1.25, U2.28
/PIN17/LCD_D16: CON1.26, U2.19
/PIN18/LCD_D17/USB_EN: CON1.27, R21.2, U2.20, U3.4
/PIN19/LCD_DOTCLK: CON2.30, U2.17
/PIN20/LCD_VSYNC: CON1.28, U2.16
/PIN21/LCD_HSYNC/I2C_SDA: CON1.29, DH/DS135.1, U2.15
/PIN22/LCD_EN/I2C_SCL: CH/CS135.1, CON1.30, U2.11
/PIN23/LCD_DISP: CON2.29, U2.12
/PIN24/LCD_WR: CON2.28, U2.13
/PIN25/LCD_RS: CON2.27, R4.2, U2.14
/PIN26/LCD_CS: CON2.26, U2.10
/PIN27/PWM2: CON2.25, U2.91
/PIN28/SOFT_SDA: CON2.24, DH/DS135.3, U2.31
/PIN29/SOFT_SCL: CH/CS135.3, CON2.23, U2.34
/PIN30: CON2.22, R22.1, R23.2, U2.81
/PIN31: CON2.21, U2.82
/PIN32/LRADC1: CON2.14, U2.107
/PIN33/LRADC0: CON2.13, U2.108
/PIN34/MIC: CON2.12, U2.116
/PSWITCH: R14.1, U2.119
/PWM0/DUART_RXD: CON2.4, D2.2, R13.2, U2.125
/PWM1/DUART_TXD: CON2.5, U2.126, U_DEBUG135.2
/RASN: U1.23, U2.62
/RESET: R16.2, RESET135.1
/SD_VCC: C40.2, C41.2, JTAG135.5, L2.2, SD135.4
/SJTAG_PSW: POWER135.2, R14.2, R18.2, RECOVERY135.2, RM3.1.2, SJTAG_PSW135.P$1
/SSP1_CMD: JTAG135.6, R9.1, SD135.3, U2.83
/SSP1_DATA0: JTAG135.2, RM3.3.2, SD135.7, U2.84
/SSP1_DATA1: JTAG135.1, RM3.4.2, SD135.8, U2.85
/SSP1_DATA2: JTAG135.8, RM3.2.2, SD135.1, U2.86
/SSP1_DATA3: JTAG135.7, R8.1, SD135.2, U2.87
/SSP1_SCK: JTAG135.4, SD135.5, U2.90
/SSP2_MOSI: U2.21, UEXT135.8
/SSP2_SCK: U2.33, UEXT135.9
/USB_DM: U2.123, USB_CON135.2, USB_HOST135.2
/USB_DP: U2.124, USB_CON135.3, USB_HOST135.3
/VDAC1: C44.1, CON2.6, U2.104
/VDD4P2: C9.2, C10.2, D1.K, U2.101
/VDDXTAL: C35.2, R15.2, U2.120
/WEN: U1.21, U2.77
/XTALI: C36.2, Q1.2, T1.3, U2.122
/XTALO: C37.2, Q1.1, T2.3, U2.121
GND: C1.1, C2.1, C3.1, C4.1, C5.1, C6.1, C7.1, C8.1, C9.1, C10.1, C11.1, C12.1, C13.1, C14.1, C15.1, C16.1, C17.1, C18.1, C19.1, C20.1, C21.1, C22.1, C23.1, C24.1, C25.1, C26.1, C27.1, C29.1, C30.1, C31.1, C32.1, C33.1, C34.1, C35.1, C36.1, C37.1, C38.1, C39.1, C40.1, C41.1, C42.2, C43.2, C44.2, C45.-, C47.2, C48.2, C49.2, C50.2, C51.2, C52.2, C53.2, CON1.2, CON2.2, D3.A, JTAG135.3, L4.1, LIPO_BAT135.2, R1.1, R6.1, R7.1, R8.2, R17.2, R20.1, R21.1, R23.1, RM2.1.2, RM2.2.2, RM2.3.2, RM2.4.2, RM3.1.1, SD135.6, T1.2, T2.1, T2.2, U1.6, U1.12, U1.34, U1.48, U1.52, U1.58, U1.64, U1.66, U2.30, U2.35, U2.98, U2.105, U2.112, U2.118, U3.2, UEXT135.2, USB_CON135.4, USB_HOST135.4, U_DEBUG135.3, VP_0.VP, VP_1.VP, VP_2.VP, VP_3.VP, VP_4.VP, VP_5.VP, VP_6.VP, VP_7.VP, VR1.2
V+: C5.2, C6.2, C7.2, C8.2, C18.2, C19.2, C20.2, C21.2, C22.2, C23.2, C24.2, C25.2, C28.1, R2.2, R5.2, U1.1, U1.3, U1.9, U1.15, U1.18, U1.33, U1.55, U1.61, U2.38, U2.45, U2.53, U2.106
VCC: 0.2, 1.2, 2.2, 3.2, C3.2, C4.2, C15.2, C16.2, C17.2, CON1.3, L2.1, R4.1, R9.2, R13.1, R19.2, RESET135.2, RM3.2.1, RM3.3.1, RM3.4.1, U2.18, U2.92, U2.95
VPP: C51.1, CON2.3, R10.2, R11.2, R12.2, UEXT135.1, VR1.5
